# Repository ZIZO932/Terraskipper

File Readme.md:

# TerraSkipper: early design

This is one of the early designs for TerraSkipper, a mudskipper-inspired robot for agriculture. I wanted to explore using fins and a tail to move across difficult ground, with a mechanism that lowers probes to take soil measurements.

The design also explored a seed-dropping mechanism. This repo keeps the CAD, circuit files, and early control logic from that stage. The later build is in [TerraSkipper V2](https://github.com/ZIZO932/Terraskipper-V2).

## Why I started it

I was interested in how mudskippers move through places where wheels can struggle. That gave me a starting point for a robot aimed at soil monitoring in the Nile Delta.

A lot of the work was figuring out how the idea would fit into a physical body: room for the electronics, servo mounts, enough wall thickness for printing, and a slider that could lower the probes. I also had to rethink the sensors after realizing that the first ones I looked at were meant for water.

## Mechanical design

The body is hollow to make room for the controller and wiring. Servo holders support the fins and tail, and the vertical slider is intended to place the probes against the soil.

## Electronics

I used KiCad to work through the controller, servo, sensor, and power connections. Moving from a breadboard layout to a schematic made it easier to track the connections and plan the PCB.

## Code in this repo

[code logic.py](code%20logic.py) is a conceptual simulation. It prints servo movements and uses example sensor readings to show the movement and measurement sequence. It doesn't control real hardware or collect live soil data.

## Parts estimate

These are the costs recorded for this design stage, rather than current supplier prices. The sensor listing and supplier links are kept from the original parts list.

| Item | Description | Qty | Unit Price (EGP) | Unit Price (USD) | Total Price (USD) | URL | Running Total (USD) |
|------|-------------|-----|------------------|------------------|-------------------|-----|---------------------|
| Raspberry Pi Pico W | MCU (Main Controller) | 1 | 650 | 13.85 | 13.85 | https://electra.store/product/raspberry-pi-pico-w/ | 13.85 |
| MG996R Servo | High Torque Servo Motor | 5 | 200 | 4.26 | 21.30 | https://www.ram-e-shop.com/ar/shop/servo-mg996-180-mg996r-servo-motor-180deg-11-kg-cm-metal-gears-7397?srsltid=AfmBOoq1zvLpgjLLOmXDFrNQpmj2SQrDjgcnsE8VNdSKkgjMb-rjCr2f | 35.15 |
| 7 in 1 soil sensor | pH and TDS Measurement Sensor | 1 | 4500 | 95.87 | 95.87 | https://makerselectronics.com/product/industrial-soil-moisture-temperature-sensor-modbus-rtu-rs485/?campaignid=20503411856&adgroid=up&network=x&device=c&campaignname=sales_pmax&gad_source=1&gad_campaignid=20503433012&gbraid=0AAAAApRJSNFn77HI4O79RMkhUNGKsHWNO&gclid=Cj0KCQiAyvHLBhDlARIsAHxl6xqx909JpmEgYe0-mFSB0og0OA0A5Ajb2pms3LxBvvR7rJVYkLQwEe4aAsfdEALw_wcB | 131.02 |
| Breadboard & Wires | Prototyping Accessories | 1 | 300 | 6.39 | 6.39 | https://www.ram-e-shop.com/shop/bb2t4d-j140-bb-bb-2t4d-j140-breadboard-1660-tie-point-140-jumper-wire-metal-base-6755 | 137.41 |
| XL4015 Converter | Regulation Module | 1 | 95 | 2.02 | 2.02 | https://www.ram-e-shop.com/shop/dc-dc-101-dc-dc-step-down-voltage-converter-adjustable-5a-xl4015-5v-32vdc-to-0-8v-30vdc-sku-dc101-7258 | 139.43 |
| 18650 Battery | Power Source | 2 | 245 | 5.22 | 10.44 | https://www.ram-e-shop.com/shop/battery-18650-lgcm-battery-lithium-li-ion-inr18650mh1-mh1-3200mah-10a-4-2-3-7-2-5v-rechargeable-9064 | 149.87 |
| MPU-6050 | IMU | 1 | 175 | 3.73 | 3.73 | https://www.ram-e-shop.com/shop/kit-imu-mpu6050-gy521-imu-6-dof-mpu-6050-gyroscope-accelerometer-sensor-module-7076 | 153.60 |
| NEO-6M GPS | GPS Module | 1 | 563 | 12.00 | 12.00 | https://makerselectronics.com/product/ublox-hw-539-neo-6m-gps-module/?srsltid=AfmBOorZ5a90If9bXw3bXueIRVRr6BAAfuh6hryrSHD4mv6YlEpa6hi- | 165.60 |

## Files

- [CAD](CAD/) — SolidWorks assembly and STEP model
- [KiCad schematic](Mudskipper%20Circuit%20Diagram%20SCHEMATICC.kicad_sch)
- [KiCad PCB](Mudskipper%20Circuit%20Diagram%20SCHEMATICC.kicad_pcb)
- [BOM](BOM.csv)
- [Build journal](journal.md)
- [Images](Images/)

The servo-driven prototype is documented in [Mudskipper](https://github.com/ZIZO932/Mudskipper), and the later DC-motor version is in [TerraSkipper V2](https://github.com/ZIZO932/Terraskipper-V2).

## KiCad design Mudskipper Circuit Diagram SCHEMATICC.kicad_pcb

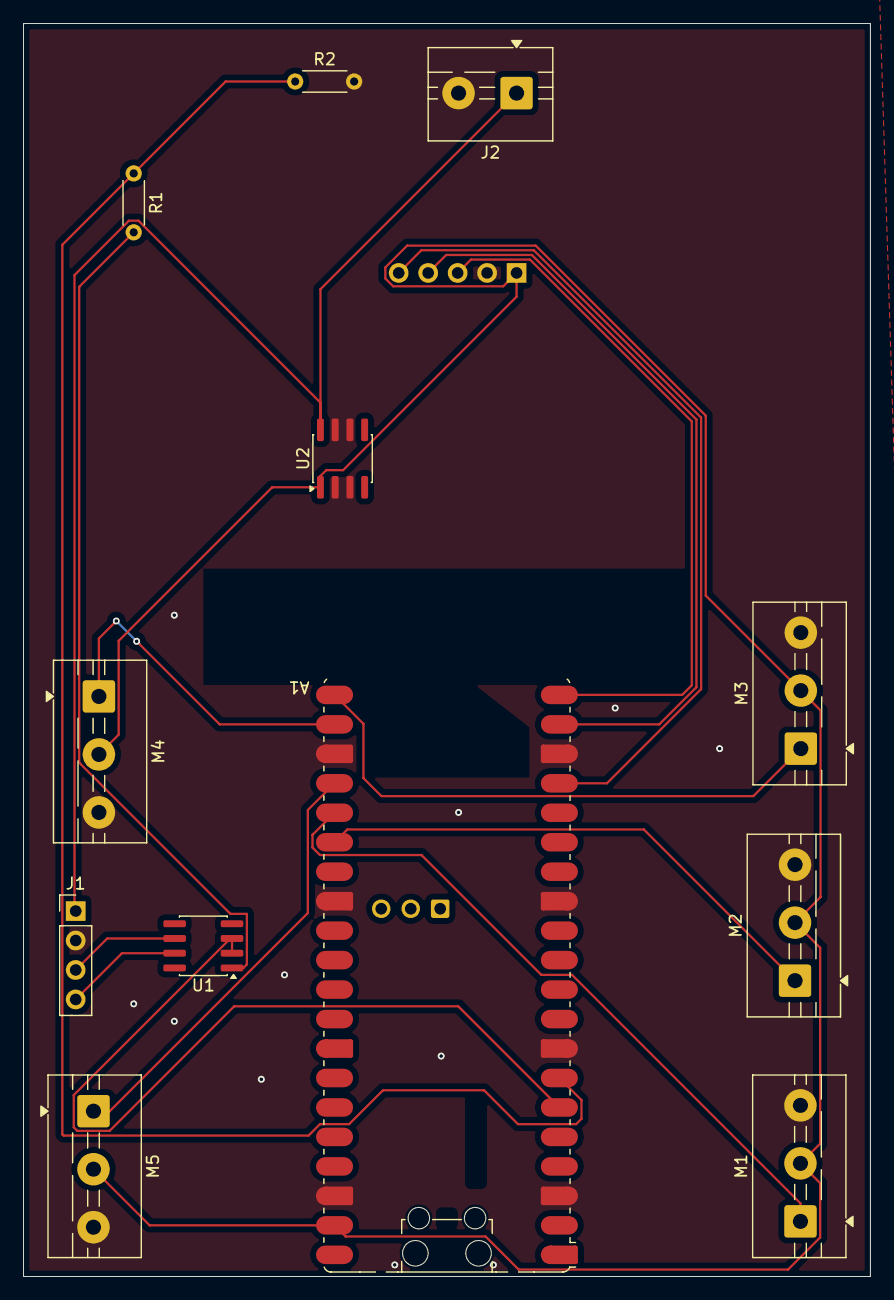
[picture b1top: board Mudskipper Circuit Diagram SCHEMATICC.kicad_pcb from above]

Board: 2 copper layers, 73.0 x 108.0 mm, 13 parts (1 on the bottom side), 16 nets.

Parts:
.1: TFT module with 5 pins; PinHeader_1x05_P2.54mm_Vertical
A1: RaspberryPi_Pico_W; RaspberryPi_Pico_W_SMD_HandSolder
J1: 7 in 1 soil sensor 12V; PinHeader_1x04_P2.54mm_Vertical
J2: Conn_01x02_Socket; TerminalBlock_MaiXu_MX126-5.0-02P_1x02_P5.00mm
M1, M2, M3, M4, M5: Motor_Servo; TerminalBlock_MaiXu_MX126-5.0-03P_1x03_P5.00mm
R1, R2: R; R_Axial_DIN0204_L3.6mm_D1.6mm_P5.08mm_Horizontal
U1: MAX485E; SOIC-8_3.9x4.9mm_P1.27mm
U2: L78L05_SO8; SOIC-8_3.9x4.9mm_P1.27mm

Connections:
+5V: .1.1, A1.39 (VSYS), M1.2 (+), M2.2 (+), M3.2 (+), M4.2 (+), M5.2 (+), U2.1 (OUT)
GND: .1.2, A1.3 (GND), A1.8 (GND), A1.13 (GND), A1.18 (GND), A1.23 (GND), A1.28 (GND), A1.38 (GND), J1.2, J2.2, M1.3 (-), M2.3 (-), M3.3 (-), M4.3 (-), M5.3 (-), R2.2, U2.2 (GND), U2.3 (GND), U2.6 (GND), U2.7 (GND)
unnamed: .1.3, A1.20 (GPIO15)
unnamed: .1.4, A1.19 (GPIO14)
unnamed: .1.5, A1.17 (GPIO13)
unnamed: A1.6 (GPIO4), U1.2 (~RE), U1.3 (DE)
unnamed: A1.7 (GPIO5), R1.1, R2.1
unnamed: A1.21 (GPIO16), M3.1 (PWM)
unnamed: A1.22 (GPIO17), M4.1 (PWM)
unnamed: A1.24 (GPIO18), M5.1 (PWM)
unnamed: A1.25 (GPIO19), M1.1 (PWM)
unnamed: A1.26 (GPIO20), M2.1 (PWM)
unnamed: J1.1, J2.1, U2.8 (IN)
unnamed: J1.3, U1.6 (A)
unnamed: J1.4, U1.7 (B)
unnamed: R1.2, U1.1 (RO)
